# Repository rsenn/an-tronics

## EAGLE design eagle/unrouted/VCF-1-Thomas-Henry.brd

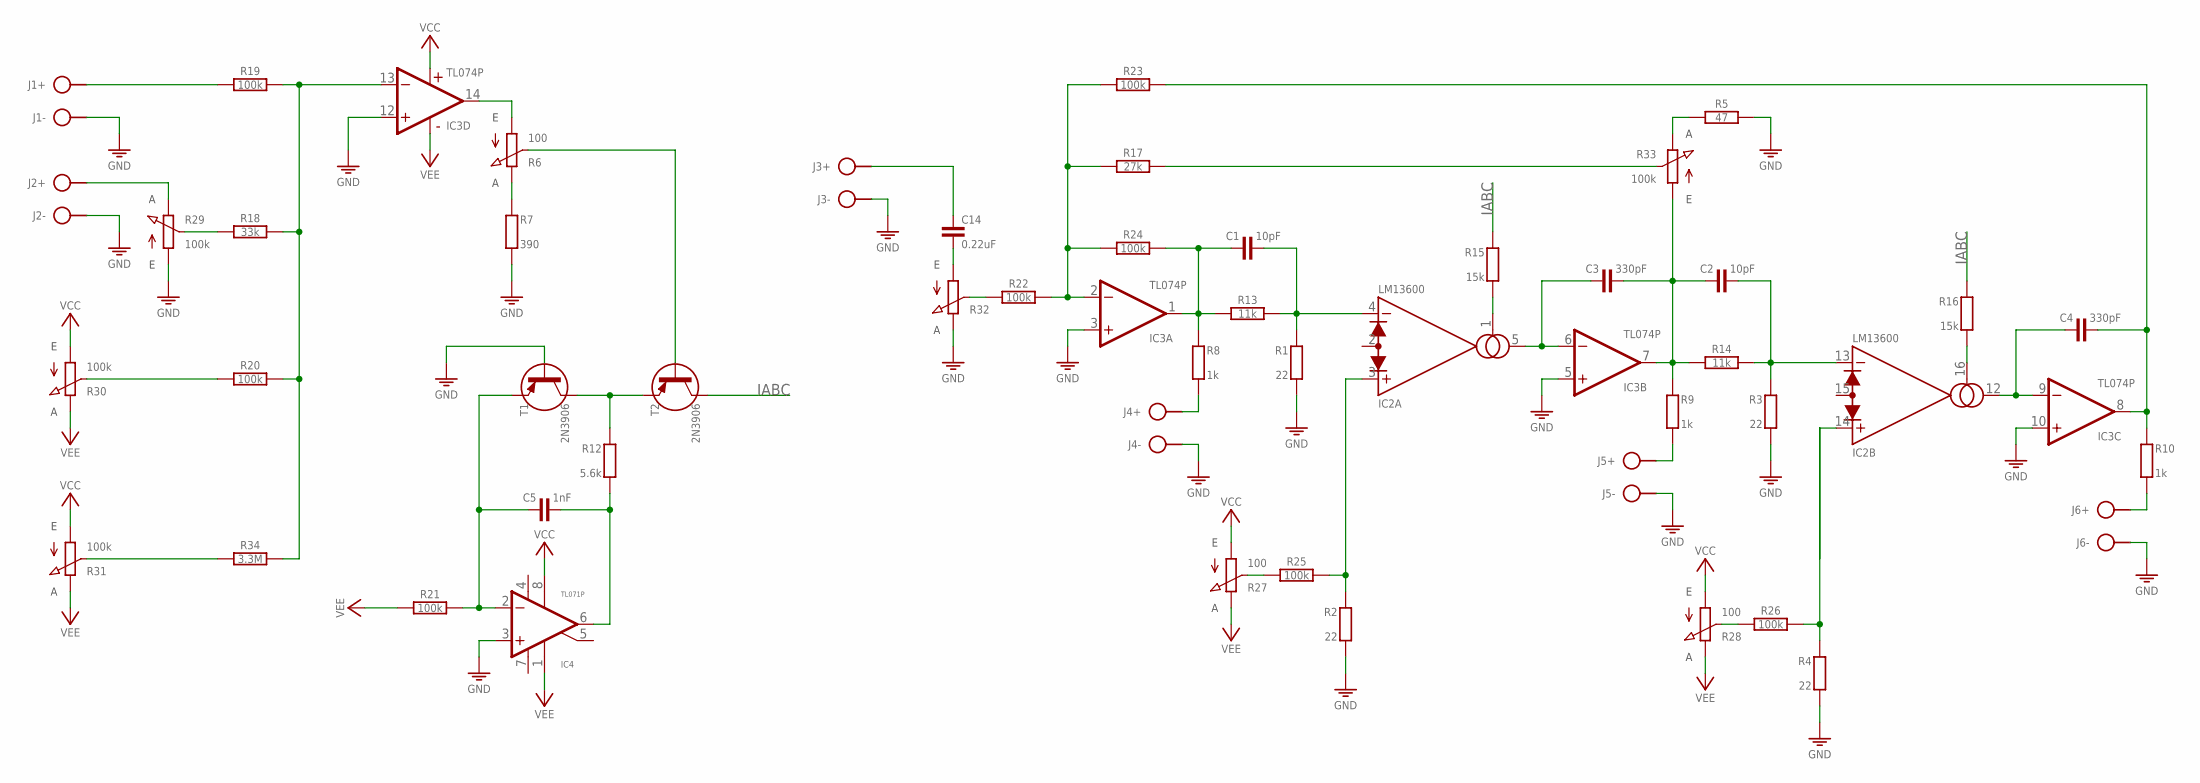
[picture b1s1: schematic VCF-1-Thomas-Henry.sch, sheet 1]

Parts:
C1, C2: 10pF; C050-020X036
C3, C4: 330pF; C050-020X036
C5: 1nF; C050-020X036
C14: 0.22uF; C050-020X044/V
IC2: LM13600; DIL16
IC3: TL074P; DIL14
IC4: TL071P; DIL08
J1, J2, J3, J4, J5, J6: SPAD+--+; SPAD-+
R1, R2, R3, R4: 22; 0204/10-V
R5: 47; 0204/10
R6, R27, R28: 100; POT-V
R7: 390; 0204/10-V
R8, R9, R10: 1k; 0204/10-V
R12: 5.6k; 0204/10-V
R13, R14: 11k; 0204/10
R15, R16: 15k; 0204/10-V
R17: 27k; 0204/10
R18: 33k; 0204/10
R19, R20, R21, R22, R23, R24, R25, R26: 100k; 0204/10
R29, R30, R31, R33: 100k; POT
R32: POT
R34: 3.3M; 0204/10
T1, T2: 2N3906; TO92

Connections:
GND: IC3.3 (+IN), IC3.5 (+IN), IC3.10 (+IN), IC3.12 (+IN), IC4.3 (+IN), J1.1, J2.1, J3.1, J4.1, J5.1, J6.1, R1.2, R2.2, R3.2, R4.2, R5.2, R7.2, R29.1 (A), R32.3 (E), T1.2 (B)
IABC: R15.1, R16.1, T2.3 (C)
unnamed: J1.2, R19.1
unnamed: R18.1, R29.2 (S)
unnamed: J2.2, R29.3 (E)
unnamed: R20.1, R30.2 (S)
unnamed: R31.2 (S), R34.1
unnamed: IC3.13 (-IN), R18.2, R19.2, R20.2, R34.2
unnamed: IC3.14 (OUT), R6.A
unnamed: R6.E, R7.1
unnamed: R12.1, T1.3 (C), T2.1 (E)
unnamed: C5.2, IC4.6 (OUT), R12.2
unnamed: C5.1, IC4.2 (-IN), R21.2, T1.1 (E)
unnamed: R6.S, T2.2 (B)
unnamed: R22.1, R32.2 (S)
unnamed: IC3.2 (-IN), R17.1, R22.2, R23.1, R24.1
unnamed: C1.1, IC3.1 (OUT), R8.1, R13.1, R24.2
unnamed: C1.2, IC2.4 (-IN), R1.1, R13.2
unnamed: J4.2, R8.2
unnamed: IC2.1 (AMP/BIAS), R15.2
unnamed: C3.1, IC2.5 (OUT), IC3.6 (-IN)
unnamed: C2.1, C3.2, IC3.7 (OUT), R9.1, R14.1, R33.1 (A)
unnamed: J5.2, R9.2
unnamed: C2.2, IC2.13 (-IN), R3.1, R14.2
unnamed: R25.1, R27.S
unnamed: IC2.3 (+IN), R2.1, R25.2
unnamed: R26.1, R28.S
unnamed: R4.1, R26.2
unnamed: IC2.16 (AMP/BIAS), R16.2
unnamed: C4.1, IC2.12 (OUT), IC3.9 (-IN)
unnamed: C4.2, IC3.8 (OUT), R10.1, R23.2
unnamed: J6.2, R10.2
unnamed: R17.2, R33.2 (S)
unnamed: R5.1, R33.3 (E)
unnamed: C14.1, J3.2
unnamed: C14.2, R32.1 (A)
V+: IC2.11 (V+), IC4.7 (V+)
V-: IC2.6 (V-), IC4.4 (V-)
VCC: IC3.4 (V+), IC4.8 (OPT), R27.A, R28.A, R30.1 (A), R31.1 (A)
VEE: IC3.11 (V-), IC4.1 (ON1), R21.1, R27.E, R28.E, R30.3 (E), R31.3 (E)

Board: 2 copper layers, 50 parts (0 on the bottom side), 40 nets, no tracks yet.

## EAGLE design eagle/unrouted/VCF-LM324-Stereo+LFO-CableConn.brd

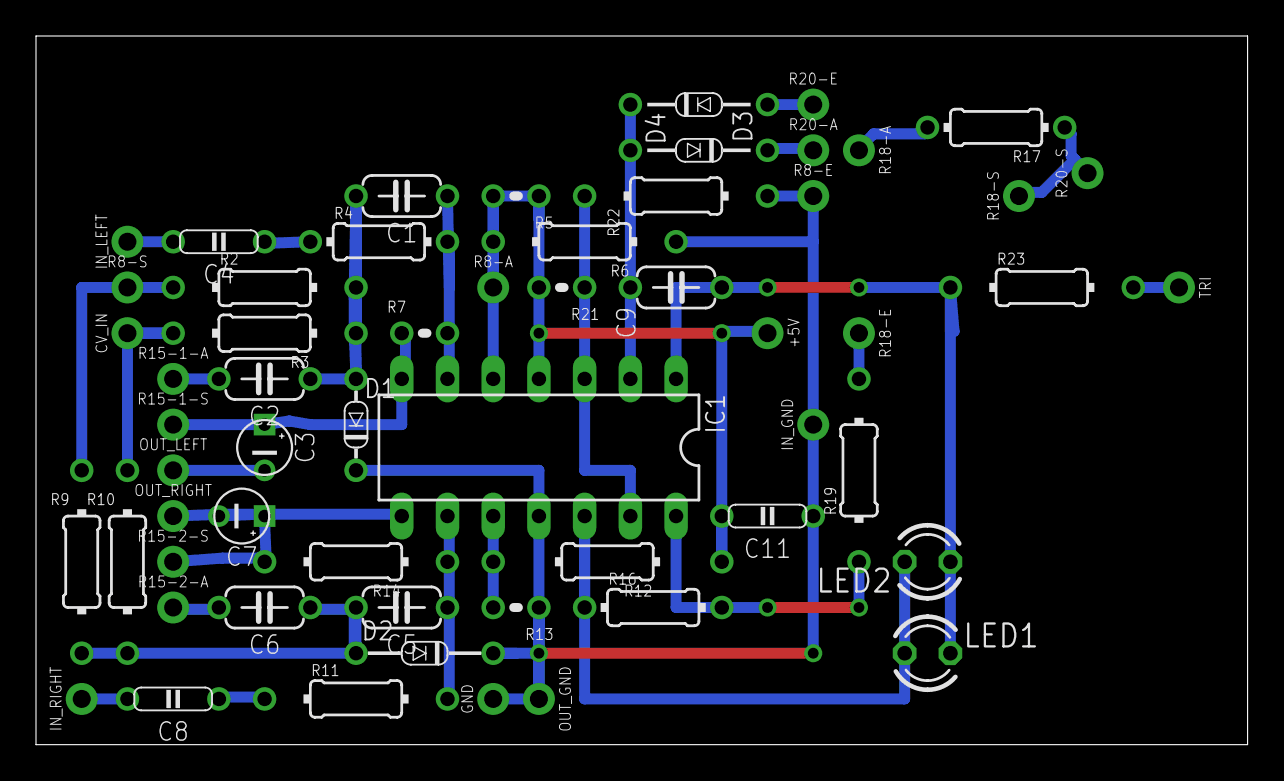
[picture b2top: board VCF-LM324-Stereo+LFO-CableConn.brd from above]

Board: 2 copper layers, 67.3 x 39.4 mm, 58 parts (0 on the bottom side), 31 nets.

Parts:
+5V: VCC; SPAD
C1, C2, C5, C6: 100nF; C050-024X044
C3, C7: 1uF; E2,5-3
C4, C8: 1uF; C050-020X044
C9: 1uF; C050-024X044/V
C11: 100nF; C050-020X044
CV_IN: CV_IN; SPAD
D1: 1N4148; DO34-5V
D2: 1N4148; DO34-7
D3, D4: 1N4148; DO34-7V
GND: GND; SPAD
IC1: LM324; DIL14
IN_GND: SPAD
IN_LEFT: SPAD
IN_RIGHT: SPAD
LED1, LED2: LED3MM
OUT_GND: SPAD
OUT_LEFT: SPAD
OUT_RIGHT: SPAD
R2, R3, R23: 1k; 0204/10
R4: 470k; 0204/7
R5, R7, R13, R21: 100k; 0204V
R6, R14: 100k; 0204/10
R8-A, R8-E, R8-S, R15-1-A, R15-1-S, R15-2-A, R15-2-S, R18-A, R18-E, R18-S, R20-A, R20-E, R20-S: SPAD
R9, R10: 1k; 0204/10-V
R11: 470k; 0204/10
R12: 100k; 0204/12
R16: 47k; 0204/7
R17: 4.7k; 0204/7-V
R19: 4.7k; 0204/10
R22: 100k; 0204/10-V
TRI: TRIANGLE; SPAD

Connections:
CV_IN: CV_IN.1, R3.2, R10.1
GND: C11.2, D1.C, D2.C, GND.1, IC1.11, IN_GND.1, OUT_GND.1, R6.1, R8-E.1, R13.1, R22.2
LEFT_IN: C4.1, IN_LEFT.1
LEFT_OUT: C3.-, OUT_LEFT.1
unnamed: R17.1, R18-A.1
unnamed: C1.1, IC1.6, R4.2, R7.2
unnamed: C2.2, R15-1-A.1
unnamed: C3.+, IC1.7, R7.1, R15-1-S.1
unnamed: R2.1, R8-S.1, R9.1
unnamed: R18-E.1, R19.2
unnamed: IC1.5, R5.2, R6.2
unnamed: C1.2, C2.1, D1.A, R2.2, R3.1
unnamed: C4.2, R4.1
unnamed: C6.2, R15-2-A.1
unnamed: C7.+, IC1.8, R14.2, R15-2-S.1
unnamed: IC1.10, R12.2, R13.2
unnamed: IC1.14, R16.2, R19.1
unnamed: IC1.12, LED1.A, LED2.K, R16.1
unnamed: C5.2, C6.1, D2.A, R9.2, R10.2
unnamed: C5.1, IC1.9, R11.2, R14.1
unnamed: R23.2, TRI.1
unnamed: C8.2, R11.1
unnamed: C9.1, D3.C, D4.A, IC1.2
unnamed: C9.2, IC1.1, LED1.K, LED2.A, R23.1
OA_C_IN+: IC1.3, IC1.13, R21.1, R22.1
RIGHT_IN: C8.1, IN_RIGHT.1
RIGHT_OUT: C7.-, OUT_RIGHT.1
TRIM_1_A: D3.A, R20-E.1
TRIM_1_B: D4.C, R20-A.1
TRIM_P: R17.2, R18-S.1, R20-S.1
VCC: +5V.1, C11.1, IC1.4, R5.1, R8-A.1, R12.1, R21.2

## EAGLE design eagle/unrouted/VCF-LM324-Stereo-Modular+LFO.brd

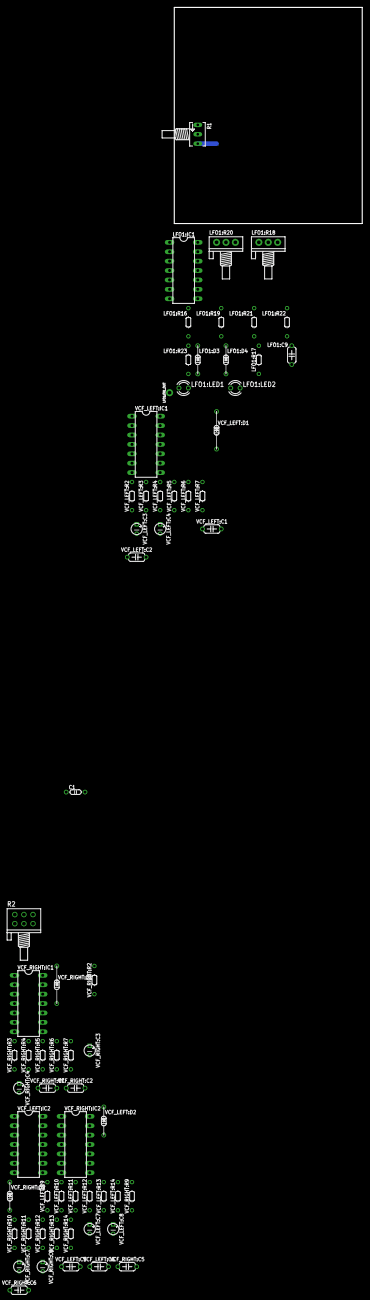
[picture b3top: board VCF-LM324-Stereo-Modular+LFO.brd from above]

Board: 2 copper layers, 50.8 x 58.4 mm, 66 parts (0 on the bottom side), 36 nets.

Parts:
C1: 100nF; C050-020X036
LFO1:C9: 1uF; C050-024X044/V
LFO1:D3, LFO1:D4: 1N4148; DO34-7V
LFO1:IC1: LM324; DIL14
LFO1:LED1, LFO1:LED2: LED3MM
LFO1:R16: 47k; 0202/7-V
LFO1:R17: 4.7k; 0202/7
LFO1:R18: 10k; POT
LFO1:R19: 4.7k; 0202/7-V
LFO1:R20: 100k; POT
LFO1:R21, LFO1:R22: 100k; 0202/7-V
LFO1:R23: 1k; 0202/7-V
LFO1:TRI_OUT: TRIANGLE; SPAD
R1: 100k; B64Y
R2: 10k; POT-STEREO
VCF_LEFT:C1, VCF_LEFT:C2, VCF_LEFT:C5, VCF_LEFT:C6: 100nF; C050-024X044
VCF_LEFT:C3, VCF_LEFT:C4, VCF_LEFT:C7, VCF_LEFT:C8: 1uF; E2,5-3
VCF_LEFT:D1: 1N4148; DO34-10V
VCF_LEFT:D2: 1N4148; DO34-7V
VCF_LEFT:IC1, VCF_LEFT:IC2: LM324; DIL14
VCF_LEFT:R2, VCF_LEFT:R3, VCF_LEFT:R9, VCF_LEFT:R10: 1k; 0202/7
VCF_LEFT:R4, VCF_LEFT:R11: 470k; 0202/7
VCF_LEFT:R5, VCF_LEFT:R6, VCF_LEFT:R7, VCF_LEFT:R12, VCF_LEFT:R13, VCF_LEFT:R14: 100k; 0202/7
VCF_RIGHT:C1, VCF_RIGHT:C2, VCF_RIGHT:C5, VCF_RIGHT:C6: 100nF; C050-024X044
VCF_RIGHT:C3, VCF_RIGHT:C4, VCF_RIGHT:C7, VCF_RIGHT:C8: 1uF; E2,5-3
VCF_RIGHT:D1: 1N4148; DO34-10V
VCF_RIGHT:D2: 1N4148; DO34-7V
VCF_RIGHT:IC1, VCF_RIGHT:IC2: LM324; DIL14
VCF_RIGHT:R2, VCF_RIGHT:R3, VCF_RIGHT:R9, VCF_RIGHT:R10: 1k; 0202/7
VCF_RIGHT:R4, VCF_RIGHT:R11: 470k; 0202/7
VCF_RIGHT:R5, VCF_RIGHT:R6, VCF_RIGHT:R7, VCF_RIGHT:R12, VCF_RIGHT:R13, VCF_RIGHT:R14: 100k; 0202/7

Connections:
CV_POT: R1.S, VCF_LEFT:R2.2, VCF_RIGHT:R2.2
GND: C1.2, LFO1:R22.1, R1.A, VCF_LEFT:D1.C, VCF_LEFT:D2.C, VCF_LEFT:IC1.11, VCF_LEFT:R6.1, VCF_LEFT:R13.1, VCF_RIGHT:D1.C, VCF_RIGHT:D2.C, VCF_RIGHT:IC1.11, VCF_RIGHT:R6.1, VCF_RIGHT:R13.1
LFO1:N$14: LFO1:IC1.7, LFO1:R16.2, LFO1:R19.1
LFO1:N$15: LFO1:IC1.5, LFO1:LED1.A, LFO1:LED2.K, LFO1:R16.1
LFO1:N$26: LFO1:C9.1, LFO1:D3.C, LFO1:D4.A, LFO1:IC1.9
LFO1:N$28: LFO1:C9.2, LFO1:IC1.8, LFO1:LED1.K, LFO1:LED2.A, LFO1:R23.2
LFO1:OA_C_IN+: LFO1:IC1.6, LFO1:IC1.10, LFO1:R21.1, LFO1:R22.2
LFO1:TRIM_1_A: LFO1:D3.A, LFO1:R20.1
LFO1:TRIM_1_B: LFO1:D4.C, LFO1:R20.3
LFO1:TRIM_2_A: LFO1:R17.1, LFO1:R18.3
LFO1:TRIM_2_B: LFO1:R18.1, LFO1:R19.2
LFO1:TRIM_P: LFO1:R17.2, LFO1:R18.2, LFO1:R20.2
unnamed: R2.1-2, R2.1-3, VCF_LEFT:C3.+, VCF_LEFT:IC1.1, VCF_LEFT:R7.2
unnamed: R2.1-1, VCF_LEFT:C2.2
unnamed: R2.2-2, R2.2-3, VCF_RIGHT:C3.+, VCF_RIGHT:IC1.1, VCF_RIGHT:R7.2
unnamed: R2.2-1, VCF_RIGHT:C2.2
unnamed: LFO1:R23.1, LFO1:TRI_OUT.1, VCF_LEFT:R3.2, VCF_RIGHT:R3.2
VCC: C1.1, LFO1:R21.2, R1.E, VCF_LEFT:IC1.4, VCF_LEFT:R5.1, VCF_LEFT:R12.1, VCF_RIGHT:IC1.4, VCF_RIGHT:R5.1, VCF_RIGHT:R12.1
VCF_LEFT:N$2: VCF_LEFT:C1.1, VCF_LEFT:IC1.2, VCF_LEFT:R4.2, VCF_LEFT:R7.1
VCF_LEFT:N$7: VCF_LEFT:IC1.3, VCF_LEFT:R5.2, VCF_LEFT:R6.2
VCF_LEFT:N$9: VCF_LEFT:C1.2, VCF_LEFT:C2.1, VCF_LEFT:D1.A, VCF_LEFT:R2.1, VCF_LEFT:R3.1
VCF_LEFT:N$10: VCF_LEFT:C4.-, VCF_LEFT:R4.1
VCF_LEFT:N$13: VCF_LEFT:IC2.13, VCF_LEFT:R12.2, VCF_LEFT:R13.2
VCF_LEFT:N$16: VCF_LEFT:C5.2, VCF_LEFT:C6.1, VCF_LEFT:D2.A, VCF_LEFT:R9.1, VCF_LEFT:R10.1
VCF_LEFT:N$17: VCF_LEFT:C5.1, VCF_LEFT:IC2.12, VCF_LEFT:R11.2, VCF_LEFT:R14.1
VCF_LEFT:N$20: VCF_LEFT:C8.-, VCF_LEFT:R11.1
VCF_LEFT:R_P_R_IN: VCF_LEFT:C7.+, VCF_LEFT:IC2.14, VCF_LEFT:R14.2
VCF_RIGHT:N$2: VCF_RIGHT:C1.1, VCF_RIGHT:IC1.2, VCF_RIGHT:R4.2, VCF_RIGHT:R7.1
VCF_RIGHT:N$7: VCF_RIGHT:IC1.3, VCF_RIGHT:R5.2, VCF_RIGHT:R6.2
VCF_RIGHT:N$9: VCF_RIGHT:C1.2, VCF_RIGHT:C2.1, VCF_RIGHT:D1.A, VCF_RIGHT:R2.1, VCF_RIGHT:R3.1
VCF_RIGHT:N$10: VCF_RIGHT:C4.-, VCF_RIGHT:R4.1
VCF_RIGHT:N$13: VCF_RIGHT:IC2.13, VCF_RIGHT:R12.2, VCF_RIGHT:R13.2
VCF_RIGHT:N$16: VCF_RIGHT:C5.2, VCF_RIGHT:C6.1, VCF_RIGHT:D2.A, VCF_RIGHT:R9.1, VCF_RIGHT:R10.1
VCF_RIGHT:N$17: VCF_RIGHT:C5.1, VCF_RIGHT:IC2.12, VCF_RIGHT:R11.2, VCF_RIGHT:R14.1
VCF_RIGHT:N$20: VCF_RIGHT:C8.-, VCF_RIGHT:R11.1
VCF_RIGHT:R_P_R_IN: VCF_RIGHT:C7.+, VCF_RIGHT:IC2.14, VCF_RIGHT:R14.2

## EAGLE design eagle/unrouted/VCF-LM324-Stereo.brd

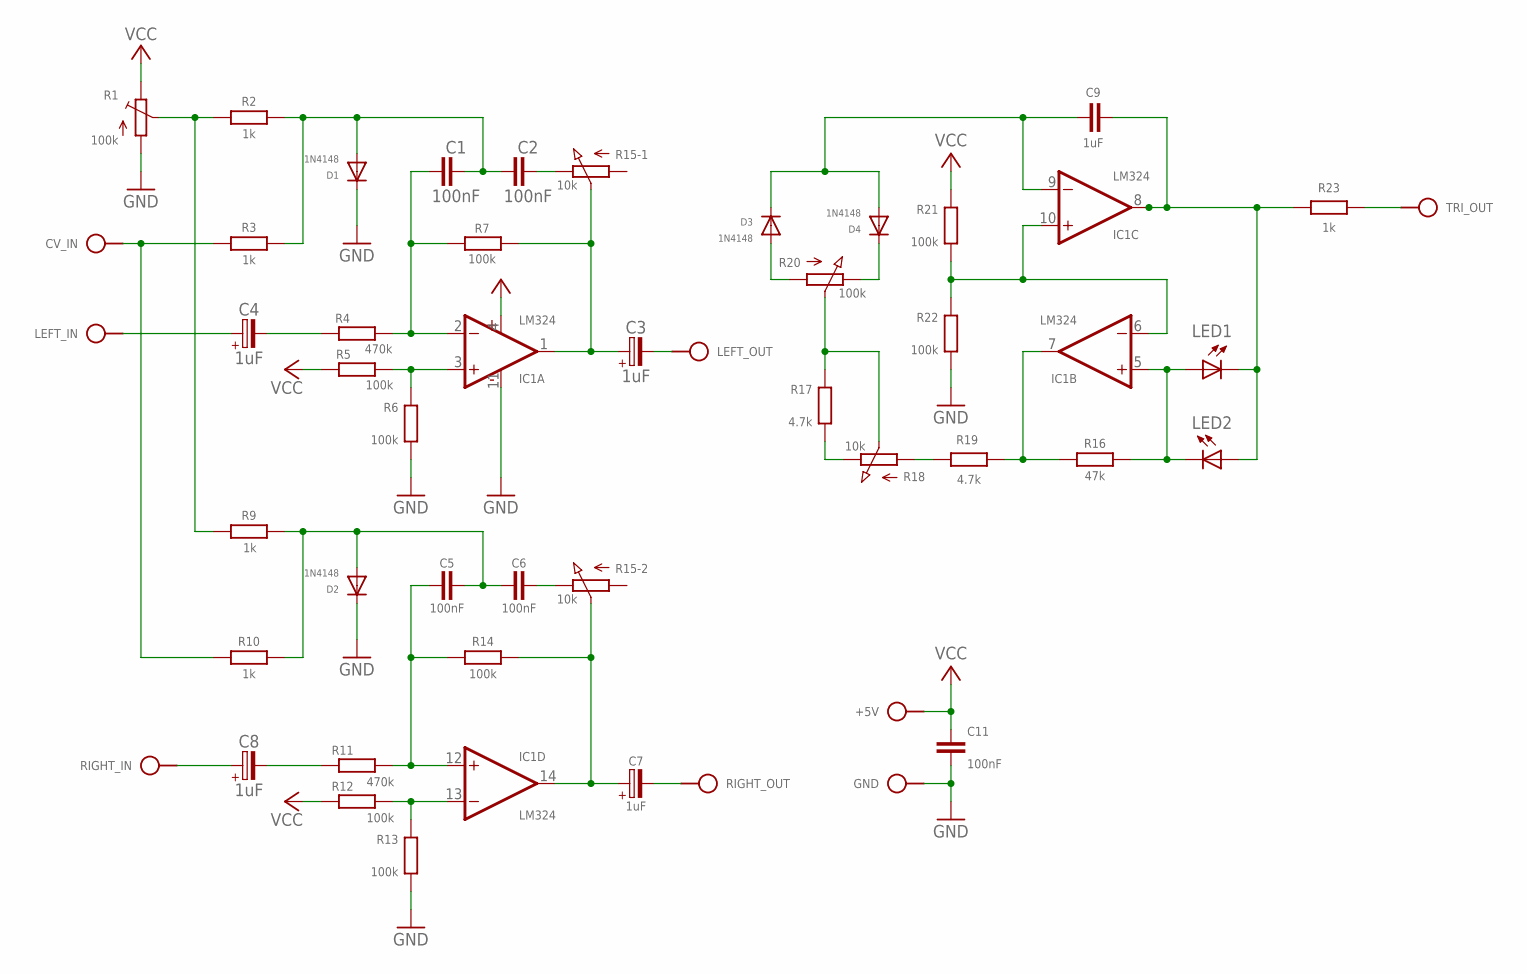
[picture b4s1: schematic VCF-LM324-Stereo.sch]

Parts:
+5V: VCC; SPAD
C1, C2, C5, C6: 100nF; C050-024X044
C3, C4, C7, C8: 1uF; E2,5-3
C9: 1uF; C050-024X044/V
C11: 100nF; C050-020X036
CV_IN: CV_IN; SPAD
D1: 1N4148; DO34-10V
D2, D3, D4: 1N4148; DO34-7V
GND: GND; SPAD
IC1: LM324; DIL14
LED1, LED2: LED3MM
LEFT_IN: AUDIO_IN; SPAD
LEFT_OUT: AUDIO_OUT; SPAD
R1: 100k; B64Y
R2, R3: 1k; 0202/7
R4, R11: 470k; 0202/7
R5, R6, R7, R12, R13, R14: 100k; 0202/7
R9, R10: 1k; 0202/10
R15: 10k; POT-STEREO-2X3
R16: 47k; 0202/7-V
R17: 4.7k; 0202/7
R18: 10k; POT
R19: 4.7k; 0202/7-V
R20: 100k; POT
R21, R22: 100k; 0202/7-V
R23: 1k; 0202/7-V
RIGHT_IN: AUDIO_IN; SPAD
RIGHT_OUT: AUDIO_OUT; SPAD
TRI_OUT: TRIANGLE; SPAD

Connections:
GND: C11.2, D1.C, D2.C, GND.1, IC1.11 (V-), R1.A, R6.1, R13.1, R22.1
unnamed: C4.+, LEFT_IN.1
unnamed: C1.1, IC1.2 (-IN), R4.2, R7.1
unnamed: C2.2, R15.1-E (E)
unnamed: C3.+, IC1.1 (OUT), R7.2, R15.1-S (S)
unnamed: R1.S, R2.2, R9.2
unnamed: C3.-, LEFT_OUT.1
unnamed: IC1.3 (+IN), R5.2, R6.2
unnamed: CV_IN.1, R3.2, R10.2
unnamed: C1.2, C2.1, D1.A, R2.1, R3.1
unnamed: C4.-, R4.1
unnamed: C6.2, R15.2-E (E)
unnamed: C7.+, IC1.14 (OUT), R14.2, R15.2-S (S)
unnamed: IC1.13 (-IN), R12.2, R13.2
unnamed: IC1.7 (OUT), R16.2, R19.1
unnamed: IC1.5 (+IN), LED1.A, LED2.K (C), R16.1
unnamed: C5.2, C6.1, D2.A, R9.1, R10.1
unnamed: C5.1, IC1.12 (+IN), R11.2, R14.1
unnamed: C7.-, RIGHT_OUT.1
unnamed: C8.+, RIGHT_IN.1
unnamed: C8.-, R11.1
unnamed: C9.1, D3.C, D4.A, IC1.9 (-IN)
unnamed: C9.2, IC1.8 (OUT), LED1.K (C), LED2.A, R23.2
OA_C_IN+: IC1.6 (-IN), IC1.10 (+IN), R21.1, R22.2
TRIM_1_A: D3.A, R20.1 (A)
TRIM_1_B: D4.C, R20.3 (E)
TRIM_2_A: R17.1, R18.3 (E)
TRIM_2_B: R18.1 (A), R19.2
TRIM_P: R17.2, R18.2 (S), R20.2 (S)
TRI_OUT: R23.1, TRI_OUT.1
VCC: +5V.1, C11.1, IC1.4 (V+), R1.E, R5.1, R12.1, R21.2

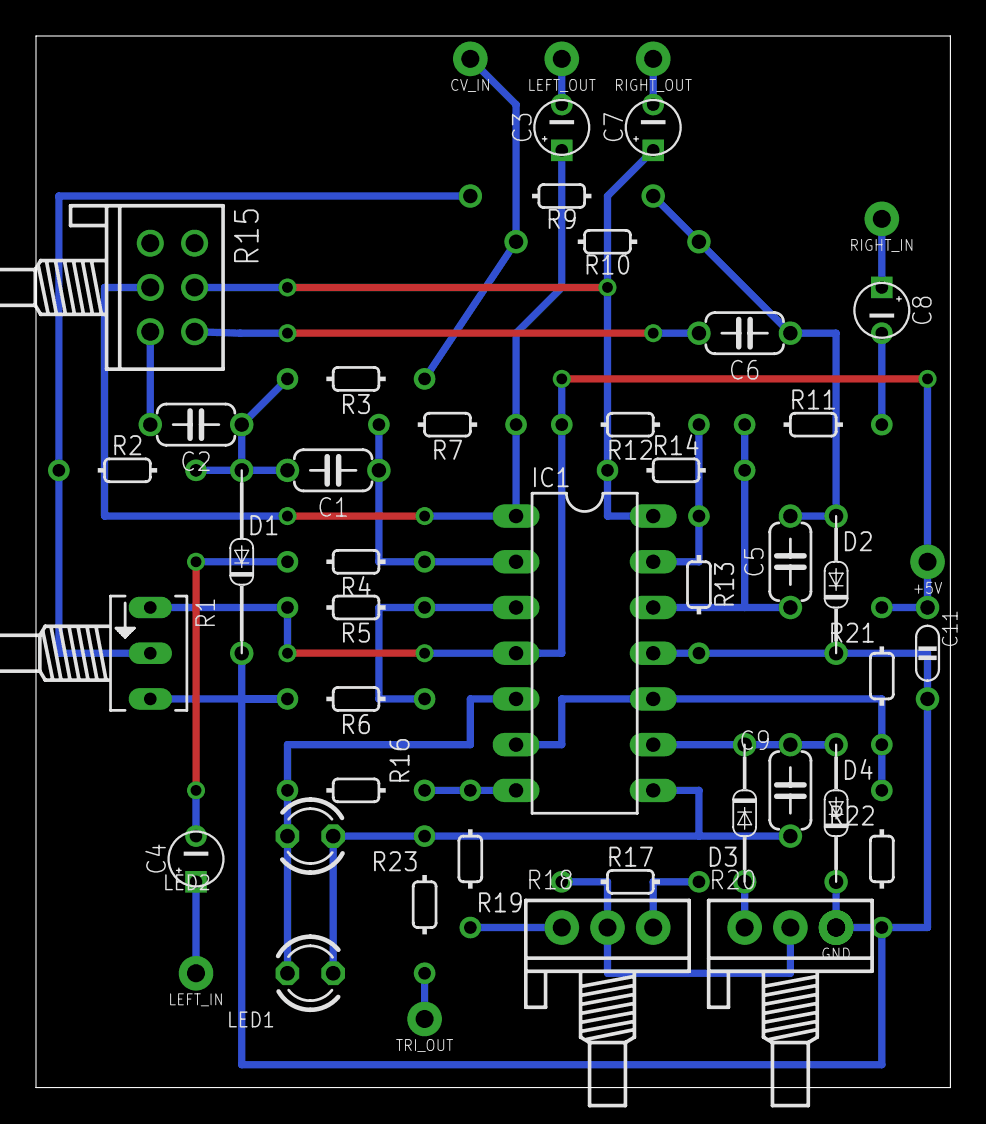
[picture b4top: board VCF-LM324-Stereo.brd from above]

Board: 2 copper layers, 50.8 x 58.4 mm, 47 parts (0 on the bottom side), 31 nets.

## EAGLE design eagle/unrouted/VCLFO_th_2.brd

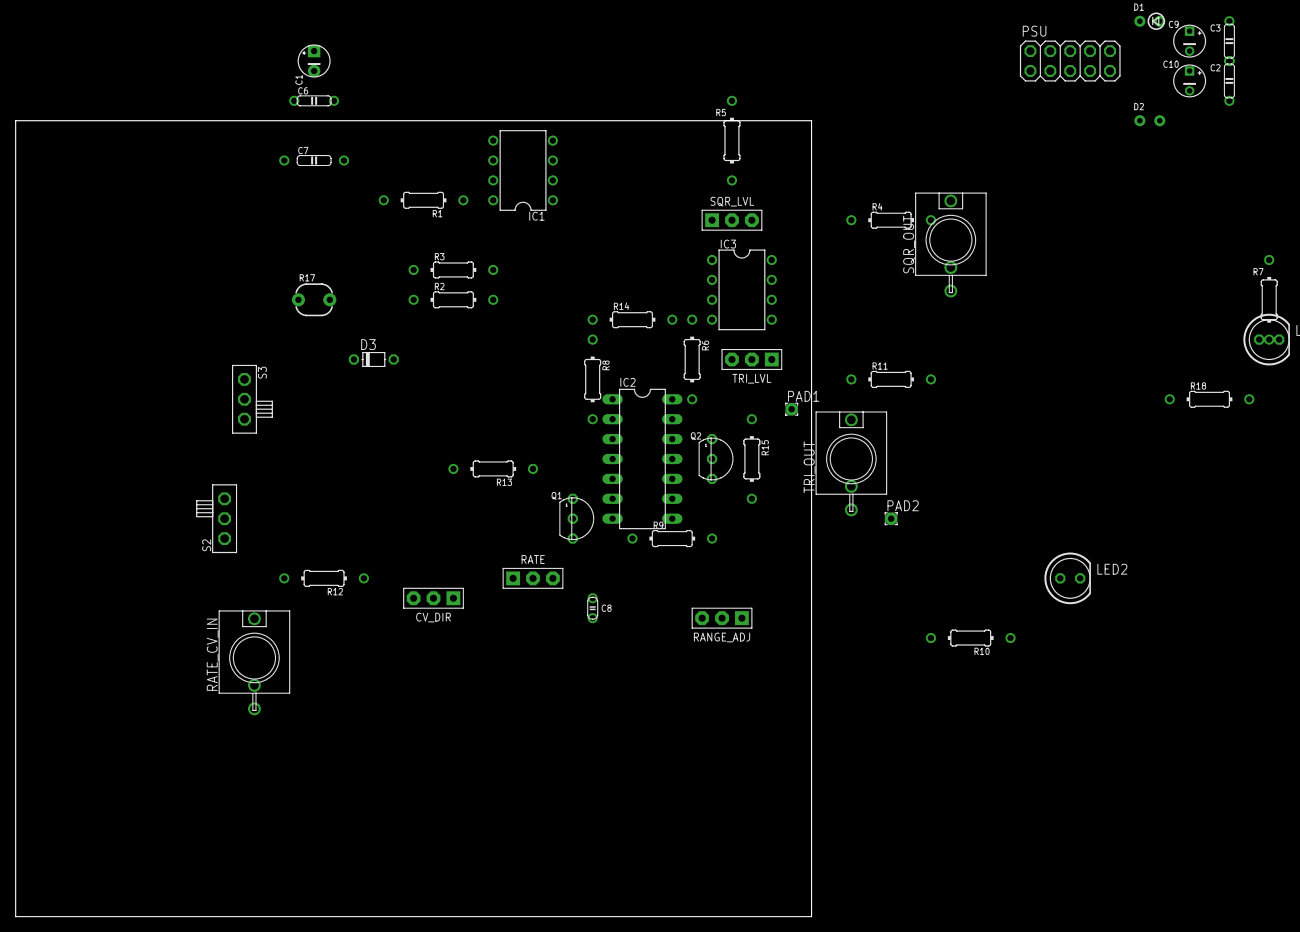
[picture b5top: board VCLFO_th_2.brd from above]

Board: 2 copper layers, 101.6 x 101.6 mm, 48 parts (0 on the bottom side), 35 nets, no tracks yet.

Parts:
C1: 10u bipolar; E2,5-4
C2, C3: 100n; C050-020X044/V
C6: 220nF; C050-020X044
C7: 4,7nF; C0750-020X044
C8: 100p; C025-015X024
C9, C10: 10u; E2.5-4/V
CV_DIR: 10k; CONN-3P
D1: Diode 1A 50V; DO35-2_54
D2: Diode 1A 50V; DO35-2_54A
D3: 1N4148; D-5
IC1, IC3: LM358N; DIL08
IC2: LM324N; DIL14
LED1, LED2: LED5MM
PAD1, PAD2: 1,6/0,8
PSU: 2X05
Q1, Q2: 2N3904; TO92
R1: 33k; 0204/10
R2, R4, R11: 1k; 0204/10
R3, R8, R12, R14, R15, R18: 100k; 0204/10
R5: 220k; 0204/10-V
R6: 4k7; 0204/10
R7: 27k; 0204/10-V
R9, R10: 10k; 0204/10
R13: 330k; 0204/10
R17: Token PGM5539; PHOTOCELL
RANGE_ADJ: 10k; CONN-3P
RATE: 10k; CONN-3P
RATE_CV_IN: WQP-PJ301M-12_JACK
S2: SKS07SP; SLSW-1P2T-H
S3: SKS04SP; SLSW-1P2T-H
SQR_LVL: 100k; CONN-3P
SQR_OUT: WQP-PJ301M-12_JACK
TRI_LVL: 100k; CONN-3P
TRI_OUT: WQP-PJ301M-12_JACK

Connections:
+12V: C3.1, C9.+, D1.C, IC1.8, IC2.4, IC3.8, R7.1
-12V: C2.2, C10.-, D2.A, IC1.4, IC2.11, IC3.4, RANGE_ADJ.3, RATE.3
GND: C2.1, C3.2, C9.-, C10.+, IC1.2, IC1.5, IC2.3, IC2.5, IC2.12, PSU.3, PSU.4, PSU.5, PSU.6, PSU.7, PSU.8, Q2.1, R10.2, RATE.1, RATE_CV_IN.P$2, RATE_CV_IN.P$3, SQR_LVL.1, SQR_OUT.P$3, TRI_LVL.1, TRI_OUT.P$3
unnamed: C7.1, IC1.6, R17.1, S2.2, S3.2
unnamed: D3.C, R2.2, R17.2
unnamed: IC3.1, IC3.2, R4.2
unnamed: R5.2, SQR_LVL.3
unnamed: IC1.3, R1.1, R3.2
unnamed: R4.1, SQR_OUT.P$1
unnamed: CV_DIR.3, IC2.2, R8.2
unnamed: IC3.6, IC3.7, R11.2
unnamed: IC3.3, SQR_LVL.2
unnamed: D1.A, PSU.1, PSU.2
unnamed: D2.C, PSU.9, PSU.10
unnamed: R12.2, RATE_CV_IN.P$1
unnamed: C8.2, IC2.14, PAD1.1, Q1.2, Q1.3, R6.2
unnamed: C1.+, S2.1
unnamed: CV_DIR.2, R12.1
unnamed: D3.A, S3.1
unnamed: R11.1, TRI_OUT.P$1
unnamed: R13.1, RATE.2
unnamed: C6.1, S2.3
unnamed: Q2.2, R18.1
unnamed: IC2.6, Q1.1, R9.1
unnamed: IC2.1, R8.1, R14.1
unnamed: C8.1, CV_DIR.1, IC2.13, R6.1, R13.2, R14.2, R15.1
unnamed: IC2.7, IC2.10, PAD2.1, R9.2
unnamed: R15.2, RANGE_ADJ.2
unnamed: IC2.8, LED2.K
unnamed: IC2.9, LED2.A, R10.1
unnamed: IC3.5, TRI_LVL.2
unnamed: LED1.K, Q2.3
unnamed: LED1.A, R7.2
SQR: IC1.1, R2.1, R3.1, R5.1
TRI: C1.-, C6.2, C7.2, IC1.7, R1.2, R18.2, TRI_LVL.3

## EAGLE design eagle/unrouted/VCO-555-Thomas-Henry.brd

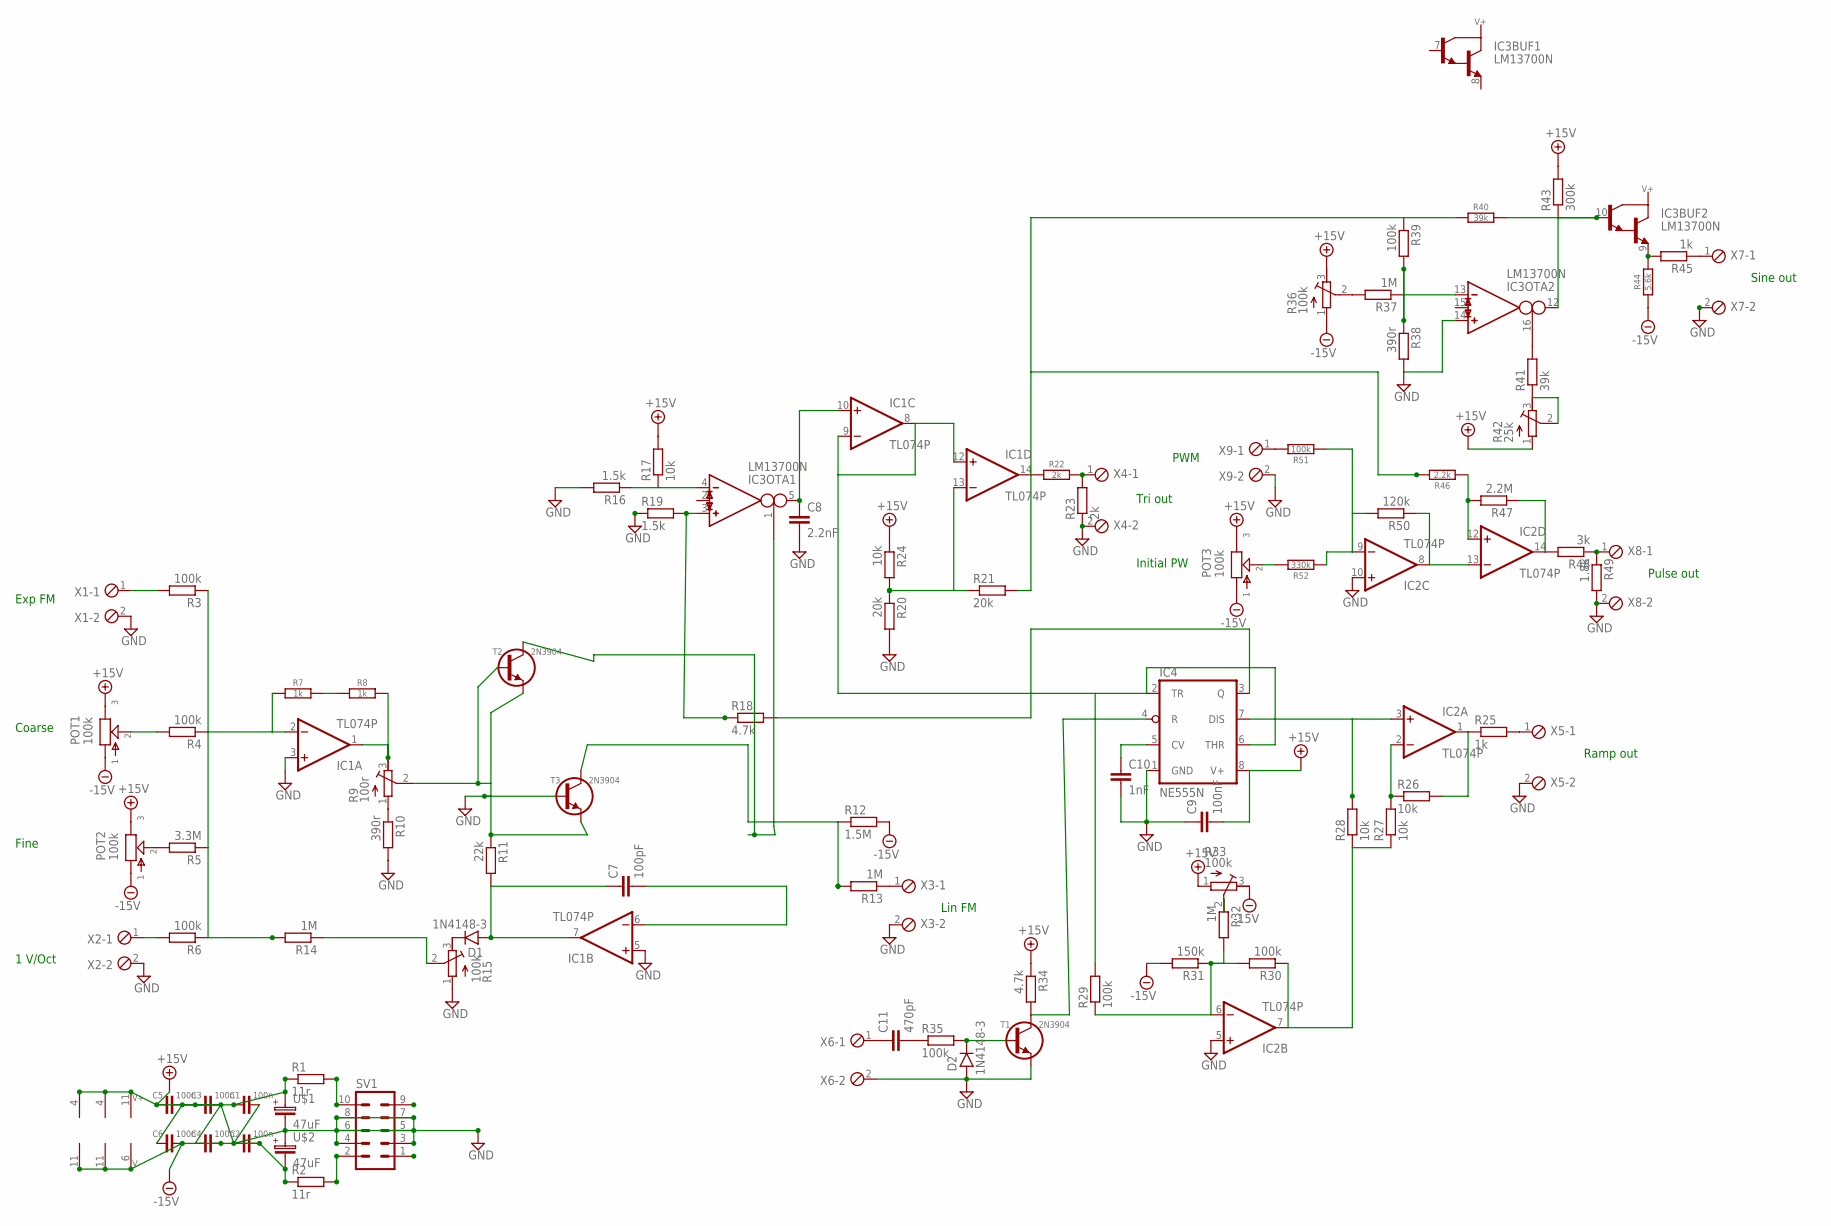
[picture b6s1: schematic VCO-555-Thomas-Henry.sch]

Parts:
C1, C2, C3, C4, C5, C6: 100n; C050-020X044
C7: 100pF; C025-040X050
C8: 2.2nF; 072X025
C9: 100nF; 072X025
C10: 1nF; 072X025
C11: 470pF; 072X025
D1, D2: 1N4148-3; DO35-3
IC1, IC2: TL074P; DIL14
IC3: LM13700N; DIL16
IC4: NE555N; DIL08
POT1, POT2, POT3: 100k; 16MM
R1, R2: 11r; 0207/10
R3, R4, R6, R29, R30, R35, R39: 100k; 0207/10
R5: 3.3M; 0207/10
R7, R8: 1k; 0204/10
R9: 100r; RTRIM3296W
R10, R38: 390r; 0207/10
R11: 22k; 0207/10
R12: 1.5M; 0207/10
R13, R14, R32, R37: 1M; 0207/10
R15, R33, R36: 100k; RTRIM3296W
R16, R19: 1.5k; 0207/10
R17, R24, R26, R27, R28: 10k; 0207/10
R18, R34: 4.7k; 0207/10
R20, R21: 20k; 0207/10
R22: 2k; 0204/10
R23: 2k; 0207/10
R25, R45: 1k; 0207/10
R31: 150k; 0207/10
R40: 39k; 0204/10
R41: 39k; 0207/10
R42: 25k; RTRIM3296W
R43: 300k; 0207/10
R44: 5.6k; 0204/10
R46: 2.2k; 0204/10
R47: 2.2M; 0207/10
R48: 3k; 0207/10
R49: 1.8k; 0207/10
R50: 120k; 0207/10
R51: 100k; 0204/10
R52: 330k; 0204/10
SV1: ML10
T1, T2, T3: 2N3904; TO92
U$1, U$2: 47uF; 063_025
X1, X2, X3, X4, X5, X6, X7, X8, X9: MPT2; 2POL254

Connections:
+15V: C1.1, C3.1, C5.1, C9.2, IC1.4 (V+), IC2.4 (V+), IC3.11 (V+), IC4.8 (V+), POT1.3, POT2.3, POT3.3, R1.1, R17.2, R24.1, R33.1 (E), R34.1, R36.3 (A), R42.1 (E), R43.2, U$1.+
-15V: C2.2, C4.2, C6.2, IC1.11 (V-), IC2.11 (V-), IC3.6 (V-), POT1.1, POT2.1, POT3.1, R2.1, R12.2, R31.2, R33.3 (A), R36.1 (E), R44.1, U$2.-
GND: C1.2, C2.1, C3.2, C4.1, C5.2, C6.1, C8.2, C9.1, C10.2, D2.A, IC1.3 (+IN), IC1.5 (+IN), IC2.5 (+IN), IC2.10 (+IN), IC3.14 (IN_P), IC4.1 (GND), R10.2, R15.1 (E), R16.2, R19.1, R20.2, R23.1, R38.2, R49.2, SV1.3, SV1.4, SV1.5, SV1.6, SV1.7, SV1.8, T1.1 (E), T3.2 (B), U$1.-, U$2.+, X1.2, X2.2, X3.2, X4.2, X5.2, X6.2, X7.2, X8.2, X9.2
unnamed: D1.C, R15.3 (A)
unnamed: R14.1, R15.2 (S)
unnamed: IC3.1 (I_BIAS), T2.3 (C)
unnamed: R2.2, SV1.2
unnamed: R1.2, SV1.10
unnamed: IC3.3 (IN_P), R18.1, R19.2
unnamed: IC3.4 (IN_N), R16.1, R17.1
unnamed: C8.1, IC1.10 (+IN), IC3.5 (OUT)
unnamed: R3.2, X1.1
unnamed: POT1.2, R4.2
unnamed: POT2.2, R5.2
unnamed: R6.2, X2.1
unnamed: IC1.2 (-IN), R3.1, R4.1, R5.1, R6.1, R7.1, R14.2
unnamed: R7.2, R8.1
unnamed: IC1.1 (OUT), R8.2, R9.3 (A)
unnamed: R9.1 (E), R10.1
unnamed: R9.2 (S), T2.2 (B)
unnamed: R11.1, T2.1 (E), T3.1 (E)
unnamed: C7.2, IC1.6 (-IN)
unnamed: R13.1, X3.1
unnamed: C7.1, D1.A, IC1.7 (OUT), R11.2
unnamed: IC1.8 (OUT), IC1.9 (-IN), IC1.12 (+IN), IC4.2 (TR), IC4.6 (THR), R29.2
unnamed: IC1.13 (-IN), R20.1, R21.1, R24.2
unnamed: IC1.14 (OUT), R21.2, R22.1, R39.1, R40.1, R46.2
unnamed: R22.2, R23.2, X4.1
unnamed: IC4.3 (Q), R18.2
unnamed: IC2.3 (+IN), IC4.7 (DIS), R28.2
unnamed: IC2.1 (OUT), R25.1, R26.2
unnamed: IC2.2 (-IN), R26.1, R27.2
unnamed: R25.2, X5.1
unnamed: IC2.6 (-IN), R29.1, R30.2, R31.1, R32.2
unnamed: R36.2 (S), R37.2
unnamed: IC2.7 (OUT), R27.1, R28.1, R30.1
unnamed: R32.1, R33.2 (S)
unnamed: C10.1, IC4.5 (CV)
unnamed: IC4.4 (R), R34.2, T1.3 (C)
unnamed: D2.C, R35.2, T1.2 (B)
unnamed: C11.2, R35.1
unnamed: C11.1, X6.1
unnamed: IC3.16 (I_BIAS), R41.2
unnamed: R41.1, R42.2 (S), R42.3 (A)
unnamed: IC2.12 (+IN), R46.1, R47.2
unnamed: IC3.13 (IN_N), R37.1, R38.1, R39.2
unnamed: IC2.14 (OUT), R47.1, R48.2
unnamed: R48.1, R49.1, X8.1
unnamed: IC3.10 (B), IC3.12 (OUT), R40.2, R43.1
unnamed: IC3.9 (E), R44.2, R45.2
unnamed: R45.1, X7.1
unnamed: IC2.8 (OUT), IC2.13 (-IN), R50.1
unnamed: IC2.9 (-IN), R50.2, R51.1, R52.1
unnamed: R51.2, X9.1
unnamed: POT3.2, R52.2
unnamed: R12.1, R13.2, T3.3 (C)

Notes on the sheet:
Exp FM
Coarse
Fine
1 V/Oct
Lin FM
Tri out
PWM
Ramp out
Pulse out
Sine out
Initial PW

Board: 2 copper layers, 87 parts (0 on the bottom side), 56 nets, no tracks yet.

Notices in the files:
parts and their libraries:
SparkFun-Sensors: Licensing: Creative Commons ShareAlike 4.0 International - https://creativecommons.org/licenses/by-sa/4.0
